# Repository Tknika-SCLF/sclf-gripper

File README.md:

# SCLF Gripper — Firmwarea

[ Euskara ](README.md) | [ English ](README.en.md) | [ Español ](README.es.md)

> Tknikaren SCLF Gripper-erako motor kontrolagailuaren firmwarea.
> STM32G474CEU6 · SimpleFOC · PlatformIO · Antigravity IDE
> Lizentzia: CC BY-SA 4.0

---

> ⚠️ **GARRANTZITSUA:** Proiektu honekin lanean hasi aurretik, mesedez irakurri beti `TASKS.md` fitxategia. Bertan aurkituko duzu proiektuaren uneko egoera zehatza eta garatzaileen arteko hurrengo urratsak zeintzuk diren.

## Hasiera Azkarra

Ingurunea konfiguratuta baduzu dagoeneko:

```bash
# 1. Konpilatu
pio run

# 2. Flasheatu (ST-Link konektatuta)
pio run --target upload

# 3. Serie-monitorea (Gripper-aren USB-C PC-ra)
pio device monitor --baud 115200
```

---

## Ingurunearen Konfigurazioa Hutsetik

### 1. Urratsa — Antigravity Instalatu

Deskargatu eta instalatu Antigravity bere webgune ofizialetik. VSCode/Windsurf-en fork bat da eta modu berean funtzionatzen du.

---

### 2. Urratsa — C/C++ Tools Instalatu

> ⚠️ PlatformIO **ez dago Open VSX-en** (Antigravity-ren marketplace-a). Bi hedapenak eskuz instalatu behar dira `.vsix` fitxategietatik.

**2a.** Joan hona: https://github.com/microsoft/vscode-cpptools/releases/latest

Deskargatu zure sistema eragileari dagokion fitxategia:

| Sistema | Deskargatu beharreko fitxategia |
|---|---|
| Windows (64-bit) | `cpptools-windows-x64.vsix` |
| macOS (Apple Silicon) | `cpptools-macOS-arm64.vsix` |
| macOS (Intel) | `cpptools-macOS-x64.vsix` |
| Linux (64-bit) | `cpptools-linux-x64.vsix` |

**2b.** Antigravity-n: `Hedapenak / Extensions (Ctrl+Shift+X)` → `···` ikonoa (hiru puntu) → **Install from VSIX** → hautatu deskargatutako `.vsix` fitxategia.

---

### 3. Urratsa — PlatformIO Instalatu

**3a.** Joan hona: https://github.com/platformio/platformio-vscode-ide/releases/latest

Ireki azken bertsioaren **"Assets"** atala eta deskargatu fitxategia (adibidez: `platformio-ide-3.3.3.vsix`).

**3b.** Antigravity-n: `Hedapenak / Extensions (Ctrl+Shift+X)` → `···` → **Install from VSIX** → hautatu deskargatutako `.vsix` fitxategia.

**3c.** Berrabiarazi Antigravity. PlatformIOk bere mendekotasunak automatikoki instalatuko ditu lehenengo aldian (2-5 minutu har ditzake).

> ⚠️ **Ohar garrantzitsua:** PlatformIOren instalazioa Antigravity-n ez dago ofizialki onartuta. Konpilazio edo igoera (upload) arazoak badituzu, kontsultatu [Arazoen Konponbidea](#arazoen-konponbidea) atala dokumentu honen amaieran.

---

### 4. Urratsa — cortex-debug Instalatu (ST-Link-ekin debug egiteko)

> 💡 **Zer da Open VSX?** Kode irekiko luzapenen erregistro alternatiboa da (Eclipse Foundation-ek kudeatua). Antigravity-k eta VSCodium-ek ofizialki erabiltzen duten biltegia da, Microsoft-en murrizketak ekiditeko, eta segurua da.

**4a.** Joan hona: https://open-vsx.org/extension/marus25/cortex-debug

Eskuin aldean dagoen **"Version"** goitibeherako menuan, hautatu **"Pre-release"** jartzen EZ duen azken bertsio egonkorra (adibidez: `1.12.1`). Ondoren, sakatu azpian agertzen den **`DOWNLOAD`** botoi morean `.vsix` fitxategia eskuratzeko.

**4b.** Instalatu aurrekoak bezala (Install from VSIX).

**4c.** OpenOCD konfiguratzea:
> 💡 **Albiste ona:** Ez duzu ezer deskargatu edo instalatu behar! PlatformIO-k automatikoki deskargatzen du OpenOCD lehenengo aldiz proiektua konpilatzen edo plakan kargatzen duzunean. Bere kokapena hau izaten da Windows-en:
`C:\Users\ZURE_ERABILTZAILEA\.platformio\packages\tool-openocd\bin\openocd.exe`

*(Cortex-Debug-ek errorea ematen badu OpenOCD ez duela aurkitzen esanez, joan Antigravity-ren ezarpenetara eta ezarri ibilbide hori `cortex-debug.openocdPath` aukeran).*

---

### 5. Urratsa — Git Instalatu

Proiektua klonatzeko Git instalatuta izan behar duzu.

**5a.** Joan hona: https://git-scm.com/downloads

**5b.** Deskargatu eta instalatu zure sistema eragilearen bertsioa (lehenetsitako aukerak mantendu ditzakezu instalazioan).

---

### 6. Urratsa — Proiektua Ireki

```bash
# Klonatu edo kopiatu firmwarearen karpeta
# Ireki Antigravity erro karpetan (platformio.ini dagoen lekuan)
```

Antigravity-n: `File → Open Folder` → hautatu `SCLF_Gripper_firmware/` karpeta.

PlatformIOk automatikoki detektatuko du `platformio.ini` eta honako hauek deskargatuko ditu:
- Platform `ststm32`
- Framework `framework-arduinoststm32`
- Toolchain `toolchain-gccarmnoneeabi`
- `SimpleFOC` liburutegia

---

### 7. Urratsa — Lehenengo Konpilazioa

Antigravity-ren beheko barran, egin klik PlatformIOren ✓ (Build) ikonoan, edo terminaletik:

```bash
pio run
```

**Espero den emaitza:**
```
[SUCCESS] Took X.XX seconds
RAM:   [=         ]  X.X% (used XXXX bytes from 131072 bytes)
Flash: [=         ]  X.X% (used XXXXX bytes from 524288 bytes)
```

Konpilatzen ez badu → ikusi [Arazoen Konponbidea](#arazoen-konponbidea).

---

### 8. Urratsa — ST-Link Konektatu eta Flasheatu

Konektatu ST-Link SCLF Gripper-aren SWD atakara:

| Pin ST-Link | Pad Gripper | Seinalea |
|---|---|---|
| SWDIO | DIO | PA13 |
| SWCLK | CLK | PA14 |
| RST | RST | PG10 |
| GND | GND | — |
| 3.3V | 3V3 | (STM32 soilik elikatzen du, ez encoderra ez driverra) |

> ⚠️ **Elikadura:**
> - ST-Link-aren 3.3V pina **nahikoa da** STM32 flasheatzeko eta encoderra (MT6701) elikatzeko. Bera bakarrik probatu dezakezu 24V konektatu gabe.
> - **BAINA** DRV8316 driverrak eta motorrak **24V kanpokoa** behar dute. Test osoetarako (motorra mugitu), beti konektatu 24V elikadura.

Flasheatu:
```bash
pio run --target upload
```

**Espero den emaitza:** `[SUCCESS]` eta D4 LEDa (PC6) keinuka hasiko da.

#### Aurre-test gomendatua: LED Heartbeat

Test konplexuak egin aurretik, egiaztatu STM32 abiarazten dela:

1. Aldatu `build_src_filter` `platformio.ini`-n:
   ```ini
   build_src_filter = +<../examples/fase0_led_heartbeat>
   ```
2. Flasheatu `pio run --target upload` erabiliz.
3. D4 LEDak 5Hz-ra keinuka egin behar du (200ms). Keinurik ez bada → elikadura edo ST-Link kableatu arazoa.
4. Berreskuratu jatorrizko `build_src_filter` Fase 1.1-era itzuli nahi duzunean.

---

### 9. Urratsa — Encoderra Egiaztatu (Fase 1.1)

> ⚠️ **Baldintzak:** ST-Link-aren 3.3V konektatuta izatea nahikoa da encoderra elikatzeko. Ez da 24V behar fase honetarako.

`fase1_1_mt6701_test`-eko firmware-ak D4 LEDa diagnostiko bisual modura erabiltzen du (Serial gabe):

1. Egiaztatu `build_src_filter` horrela dagoela `platformio.ini`-n:
   ```ini
   build_src_filter = +<../examples/fase1_1_mt6701_test> +<encoder/>
   ```
2. Flasheatu: `pio run --target upload`
3. Begiratu D4 LEDa:

| LED portaera | Esanahia |
|---|---|
| 3 keinu azkar abiaraztean | `setup()` ondo amaituta |
| LED motela (700ms, ~0.7Hz) | Motorra lehen erdibiraketan (0°-180°) |
| LED azkarra (80ms, ~6Hz) | Motorra bigarren erdibiraketan (180°-360°) |
| **Motorra biratzean aldatzen da** ✅ | **MT6701 encoderrak funtzionatzen du!** |
| Beti azkar aldaketarik gabe | SPI-k 0xFFFF bueltatzen du → encoderrak elikadurarik ez |

✅ **LEDak motorra biratzean aldatzen badu, Fase 1.1 gaindituta dago.**

### 9b. Urratsa — Serial Monitor Egiaztatu (USB VCP)

> ✅ **EGOERA:** Ondo funtzionatzen du. Firmwareak `SystemClock_Config` bloke bat dauka `main.cpp`-n STM32G4-ren USB periferikorako behar den HSI48 osziladorea gaitzeko.

1. Konektatu USB-C kable bat Gripperraren eta PCaren artean.
2. Ireki PlatformIOren serie-monitorea (🔌 ikonoa beheko barran) edo sartu:
   ```bash
   pio device monitor --baud 115200
   ```
3. Testaren irteera ikusi beharko zenuke pantailan (Adib. `MT6701 Raw (con o sin 24V): X` edo biratzean aldatzen den balio bat).

---

### 10. Urratsa — Faseen Probak eta Adibideak (`examples/`)

Proiektu honen firmware garapena fase ezberdinetan banatuta dago (ikusi `TASKS.md`). Fase bakoitzean idatzitako kode-probak (test standalone-ak) **`examples/`** karpetaren barruan gordetzen dira.

Hardware berria muntatzen baduzu edo sentsore zehatz bat probatu nahi baduzu:
1. Sartu `examples/` karpetan eta aukeratu fasea (adib. `phase1_1_mt6701_test`, `phase1_2_drv_spi`, `phase1_4_rs485_ping`, `phase3_2_rs485_control` edo `phase3_3_ur_rs485`).
2. **Irakurri karpeta horretan dagoen `README.md` fitxategia** argibide zehatzak ikusteko.
   - **Oharra (Phase 3.3):** RS485 komunikazioa 115200 baud-etan doa UR robot eta URCap/URSim integrazio probarako.
3. Kopiatu bertako `main.cpp` fitxategia eta ordezkatu zure probako `src/main.cpp` fitxategiarekin (edo erabili dagokion ingurunea `platformio.ini`-n). 
4. Konpilatu eta igo (`pio run --target upload`).

---

### 11. Urratsa — IA Agentea Konfiguratu

Antigravity-n barneratuta dagoen IA laguntzailearekin lan egiteko:

1. Ireki agentearen txat-panela (IA ikonoa alboko barran).
2. Saio bakoitzaren hasieran, idatzi:

```
Irakurri testuinguru-fitxategi hauek lagundu aurretik:
- AGENT.md   (hardwarea, pinak, arkitektura)
- MEMORY.md  (uneko egoera, kalibratutako parametroak)
- TASKS.md   (orain lantzen ari naizen zeregina)
- RULES.md   (sortutako kodeak errespetatu behar dituen arauak)
```

3. Gero, deskribatu zein zeregin landu nahi duzun `TASKS.md`-tik.

---

## Proiektuaren Egitura

```
SCLF_Gripper_firmware/
│
├── src/
│   ├── main.cpp                    ← Sarrera puntua. 0 FASEA: smoke test
│   ├── config/
│   │   └── pins.h                  ← Pin GUZTIAK. Eskematikoarekin egiaztatuta.
│   ├── encoder/
│   │   ├── MT6701.h                ← Encoder-aren APIa (eskeletoa prest)
│   │   └── MT6701.cpp              ← 1.1 FASEAN inplementatu
│   ├── motor/
│   │   ├── DRV8316.h               ← Gate driver-aren APIa (eskeletoa prest)
│   │   └── DRV8316.cpp             ← 1.2 FASEAN inplementatu
│   ├── comms/
│   │   ├── RS485.h                 ← RS-485 APIa
│   │   └── RS485.cpp               ← RS-485 inplementazioa
│   └── faults/
│       ├── FaultManager.h          ← Akats kudeatzailearen APIa (eskeletoa prest)
│       └── FaultManager.cpp        ← 6 FASEAN inplementatu
│
├── lib/                            ← Bertako liburutegiak
├── test/                           ← PlatformIO Unity testak (8 FASEA)
│
├── examples/
│   ├── phase0_led_heartbeat/        ← 0 Fasea: LED keinua menpekotasunik gabe
│   ├── phase1_1_mt6701_test/        ← 1.1 Fasea: MT6701 encoder proba SPI bidez
│   ├── phase1_2_drv_spi/            ← 1.2 Fasea: DRV8316 SPI komunikazio proba
│   ├── phase1_3_open_loop_v_control/← 1.3 Fasea: Begizta irekiko tentsio kontrola
│   ├── phase1_4_rs485_ping/         ← 1.4 Fasea: RS-485 PING/PONG oinarrizkoa
│   ├── phase2_1_foc_open_loop/      ← 2.1 Fasea: FOC begizta irekiko kontrola
│   ├── phase2_2_foc_closed_loop/    ← 2.2 Fasea: FOC begizta itxia
│   ├── phase3_1_rs485_basic/        ← 3.1 Fasea: RS-485 oinarrizko protokoloa
│   ├── phase3_2_rs485_control/      ← 3.2 Fasea: RS-485 kontrol komando osoak
│   └── phase3_3_ur_rs485/           ← 3.3 Fasea: UR Robot / URCap RS-485 integrazioa
│
├── .vscode/
│   ├── settings.json               ← IDE konfigurazioa (IntelliSense, formatua)
│   ├── extensions.json             ← Gomendatutako hedapenak
│   └── launch.json                 ← Debug ST-Link cortex-debug-ekin
│
├── platformio.ini                  ← Build eta upload konfigurazioa
├── .clang-format                   ← Kode estiloa (gordetzean aplikatzen da)
├── .gitignore
│
├── AGENT.md    ← 📋 IA agentearentzako testuingurua
├── MEMORY.md   ← 🧠 Proiektuaren egoera iraunkorra
├── TASKS.md    ← ✅ Backlog osoa faseka
├── RULES.md    ← 📏 Proiektuaren arauak
└── SRS.md      ← 📄 Eskakizunen zehaztapena
```

### Arkitektura Modularraren Azalpena

Proiektu hau berezibila eta antolatua izateko garatu da:
* **`main.cpp` ("Zuzendaria"):** FOC kontrol-begizta eta hasierako konfigurazioa soilik ditu. Ez da kode nahaspilatuz betetzen.
* **`.cpp` espezifikoak ("Musikariak"):** Txip bakoitzak bere artxibo dedikatua dauka bere funtzio jakingarriagoetarako (adibidez `MT6701.cpp` posizioa zuzenean irakurtzeko erroreak kontrolatuz, edo `DRV8316.cpp` tenperatura edo zirkuitulabur kasuez informatzeko).
* **Modu honetan:** `main.cpp`-ak oinarrizko aginduak ematen ditu, eta modulu bakoitzak badaki bere tresna zehazki nola erabili, etorkizuneko hardware aldaketak izugarri erraztuz.

### Hardware Segurtasuna eta Garapena (⚠️ OSO GARRANTZITSUA)

Antigravity barruan proiektu hau garatzean, [Arau Zorrotzak (RULES.md)](RULES.md) ezarrita daude:
1. **Debekatuta dago Blokeatzea:** Inoiz ez erabili `delay()`, `HAL_Delay` edo `while()` begizta infiniturik FOC exekuzioan. SimpleFOC-ek mikroren %100 erabiltzea eskatzen du korrontea denbora errealean kalkulatzeko. Mikroa "lotaratzeak" motorra edo driverra segundo batean erretzea ekar dezake.
2. **`foc-hardware-setup` Tresna (Skill):** Kodea garatzen hasi aurretik, gure IA laguntzaileak badu tresna espezifiko bat KiCad-eko eskema elektrikoak zuzenean irakurtzeko (`.kicad_sch`) eta `pins.h` fitxategi ezin hobea sortzeko, inolako giza-akatsik gabe. Zure laguna da, erabili proiektuaren azken pinen zehaztapenak egiaztatzeko!
3. **Cortex-Debug Magia:** ST-Link v2 klonarekin edo jatorrizkoarekin, Plaka zuzenean kontrolatu eta pausatu daiteke. Programan aldagairen batek zergatik hartzen duen balio jakin bat deskubritu nahi bada, jarri Breakpoint (eten-puntu) bat Antigravity-n, eta kodea zuzen-zuzenean pausatuko da STM32-an!

---

## PlatformIO Komando Erabilienak

```bash
pio run                          # Konpilatu
pio run --target upload          # Konpilatu eta flasheatu (ST-Link)
pio run --target upload_dfu      # USB DFU bidez flasheatu (BOOT + RST)
pio device monitor               # Serie-monitorea (USB VCP, 115200 baud)
pio test                         # Test unitarioak exekutatu
pio run --target clean           # Konpilazio-artefaktuak garbitu
pio lib install "Simple FOC"     # Eskuz instalatu liburutegia
pio pkg update                   # Plataforma eta liburutegiak eguneratu
```

---

## DFU Bootloader (Flasheatu ST-Link gabe)

ST-Link erabilgarririk ez baduzu, USB DFU bidez flashea dezakezu:

1. Mantendu sakatuta **BOOT** (PB8) botoia.
2. Sakatu eta askatu **RESET** (PG10) botoia.
3. Askatu **BOOT**.
4. Gripperra DFU gailu gisa agertuko da PCan.
5. Aldatu `upload_protocol = dfu` fitxategian `platformio.ini`.
6. Exekutatu `pio run --target upload`.

> 💡 **Oharra ST-Link gabe DFU erabiltzearen inguruan (PA9 pina):**
> Ohiko STM32etan (F1/F4), USB kablea konektatuta dagoela nabaritzeko (VBUS sensing) `PA9` pina erabiltzen da. Gure diseinuan, ordea, `PA9` pina motorraren B fasera (DRV8316) konektatuta dago (`PIN_BH`). Baina ez larritu! **STM32G4 familiak VBUS sentsorea hardware bidez desgaituta dauka** bere Bootloader nagusian (AN2606). Hori dela eta, DFU moduak primeran funtzionatuko du soilik `PA11` eta `PA12` datu-pinak erabiliz, hardware aldaketen beharrik gabe.
> 
> **⚠️ KONTUZ Arazketa (Debugging) egiteko orduan:**
> Kontuan izan USB DFU metodoa "itsu-itsuan pentsatua" dela: kodearen irudia (`.bin`) mikroaren memorian kargatzeko **soilik** balio du. Garapen-fasean zaudenean eta SimpleFOC motorraren ezusteko portaera bat ikertu behar duzunean, **ezinbestekoa da ST-Link (edo SWD) bat erabiltzea**. ST-Link batek zuzenean ARM Cortex muinera konektatzen zaitu `PA13/PA14` bidez, eta aukera ematen dizu kodea pausatzeko (Breakpoints), aldagaien balioak denbora errealean irakurtzeko eta exekuzioa lerroz lerro aztertzeko VS Code-n. USB-ak ezin du horrelakorik egin.

---

## Arazoen Konponbidea

### PlatformIOk ez du konpilatzen / toolchain errorea
```bash
# STM32 plataforma berrinstalatu
pio platform install ststm32

# Garbitu eta berriro konpilatu
pio run --target clean && pio run
```

### ST-Link-ek ez du plaka detektatzen
- Egiaztatu ST-Link-eko GNDa gripperreko GND-ra konektatuta dagoela.
- Egiaztatu plakak elikadura duela (PWR LEDa piztuta).
- Probatu `openocd -f interface/stlink.cfg -f target/stm32g4x.cfg` terminalean.
- OpenOCD-k huts egiten badu: eguneratu ST-Link firmwarea STM32CubeProgrammer-etik.

### USB VCP ez da agertzen PCan
- Instalatu STM32 VCP kontrolatzailea (driverra): https://www.st.com/en/development-tools/stsw-stm32102.html (Windows soilik)
- Linux/macOS sistemetan ez dago kontrolatzailerik behar. Egiaztatu `ls /dev/ttyACM*` erabiliz.

### LEDak ez du keinurik egiten flasheatu ondoren
- **Ziurtatu erlojuaren konfigurazioa duzula:** STM32duino framework-ak `-DUSBCON` flag-ekin (berez aktibatuta proiektu honetan) USB CDC possesses `setup()` baino **lehenago** hasieratzen du. `main.cpp`-ren amaieran HSI48 aktibatzen duen `SystemClock_Config(void)` funtzioa falta bada, firmwarea blokeatu egiten da.
- Probatu `examples/fase0_led_heartbeat` (LED soilik, menpekotasunik gabe). Horrek ere funtzionatzen ez badu → elikadura edo kableatu arazoa.

### Serial Monitoreak ez du daturik erakusten (pantaila hutsik)
- Ziurtatu COM ataka zuzenean konektatzen zarela. ST-Link-ek COM bereizi bat sortzen du: COM hori beti isilik egongo da. Bilatu "STM32 Virtual COM Port" Gailu Kudeatzailean.
- Flasheatu berri baduzu, Windows-ek segundo bat behar izan dezake USB berria ezagutzeko. PlatformIO-k ataka zaharrean monitorea ireki badu, "zintzilik" geratuko da. Kantzelatu terminalean `Ctrl+C` erabiliz eta exekutatu `pio device monitor` berriro.

### IntelliSense-k ez du `Arduino.h` edo STM32 header-ak aurkitzen
- Itxaron PlatformIOk lehenengo konpilazioa amaitu arte (includes indizea sortzen du).
- Arazoak jarraitzen badu: `Ctrl+Shift+P` → "C/C++: Reset IntelliSense Database".

### Antigravity / PlatformIO ez da plakarekin komunikatzen
- Hau komunitatean dokumentatuta dagoen arazo ezaguna da. PlatformIO Antigravity-n
  ez dago ofizialki onartuta. Konpilazioak funtzionatzen badu baina igotzeak (upload) huts egiten badu,
  saiatu `pio run --target upload` exekutatzen **barne terminaletik**, PlatformIOko
  UI botoiaren ordez.

### PlatformIOk "ms-vscode.cpptools" eskatzen du etengabe (Menpekotasunen Kirurgia)
PlatformIOk batzuetan Microsoft-en hedapena instalatzea exijitzen du, nahiz eta eskuz instalatuta izan. Arazoa konpontzeko:
1. Itxi Antigravity erabat.
2. Ireki fitxategi-esploratzailea eta joan hona: `%USERPROFILE%\.antigravity\extensions\` (Windows) edo `~/.antigravity/extensions/` (Linux/macOS).
3. Sartu `platformio.platformio-ide-...` izeneko karpetan.
4. Ireki `package.json` fitxategia testu-editore batekin.
5. Bilatu `"extensionDependencies": ["ms-vscode.cpptools"]` lerroa.
6. Utzi hutsik horrela: `"extensionDependencies": []`
7. Gorde fitxategia eta berrabiarazi Antigravity.

---

## Erreferentziazko Hardwarea

| Osagaia | Zatia | Datasheet-a |
|---|---|---|
| MCU | STM32G474CEU6 | [ST.com](https://www.st.com/resource/en/reference_manual/rm0440-stm32g4-series-advanced-armbased-32bit-mcus-stmicroelectronics.pdf) |
| Gate Driver | DRV8316CRRGFR | [TI.com](https://www.ti.com/lit/ds/symlink/drv8316.pdf) |
| Encoder | MT6701QT | [Magntek](https://www.magntek.com.cn/upload/MT6701_Rev.1.8.pdf) |
| RS-485 | MAX3485 | [Analog](https://www.analog.com/media/en/technical-documentation/data-sheets/MAX3483-MAX3491.pdf) |
| SimpleFOC | v2.x | [docs.simplefoc.com](https://docs.simplefoc.com) |

---

*Tknikak diseinatua — Licensed under CC BY-SA 4.0*

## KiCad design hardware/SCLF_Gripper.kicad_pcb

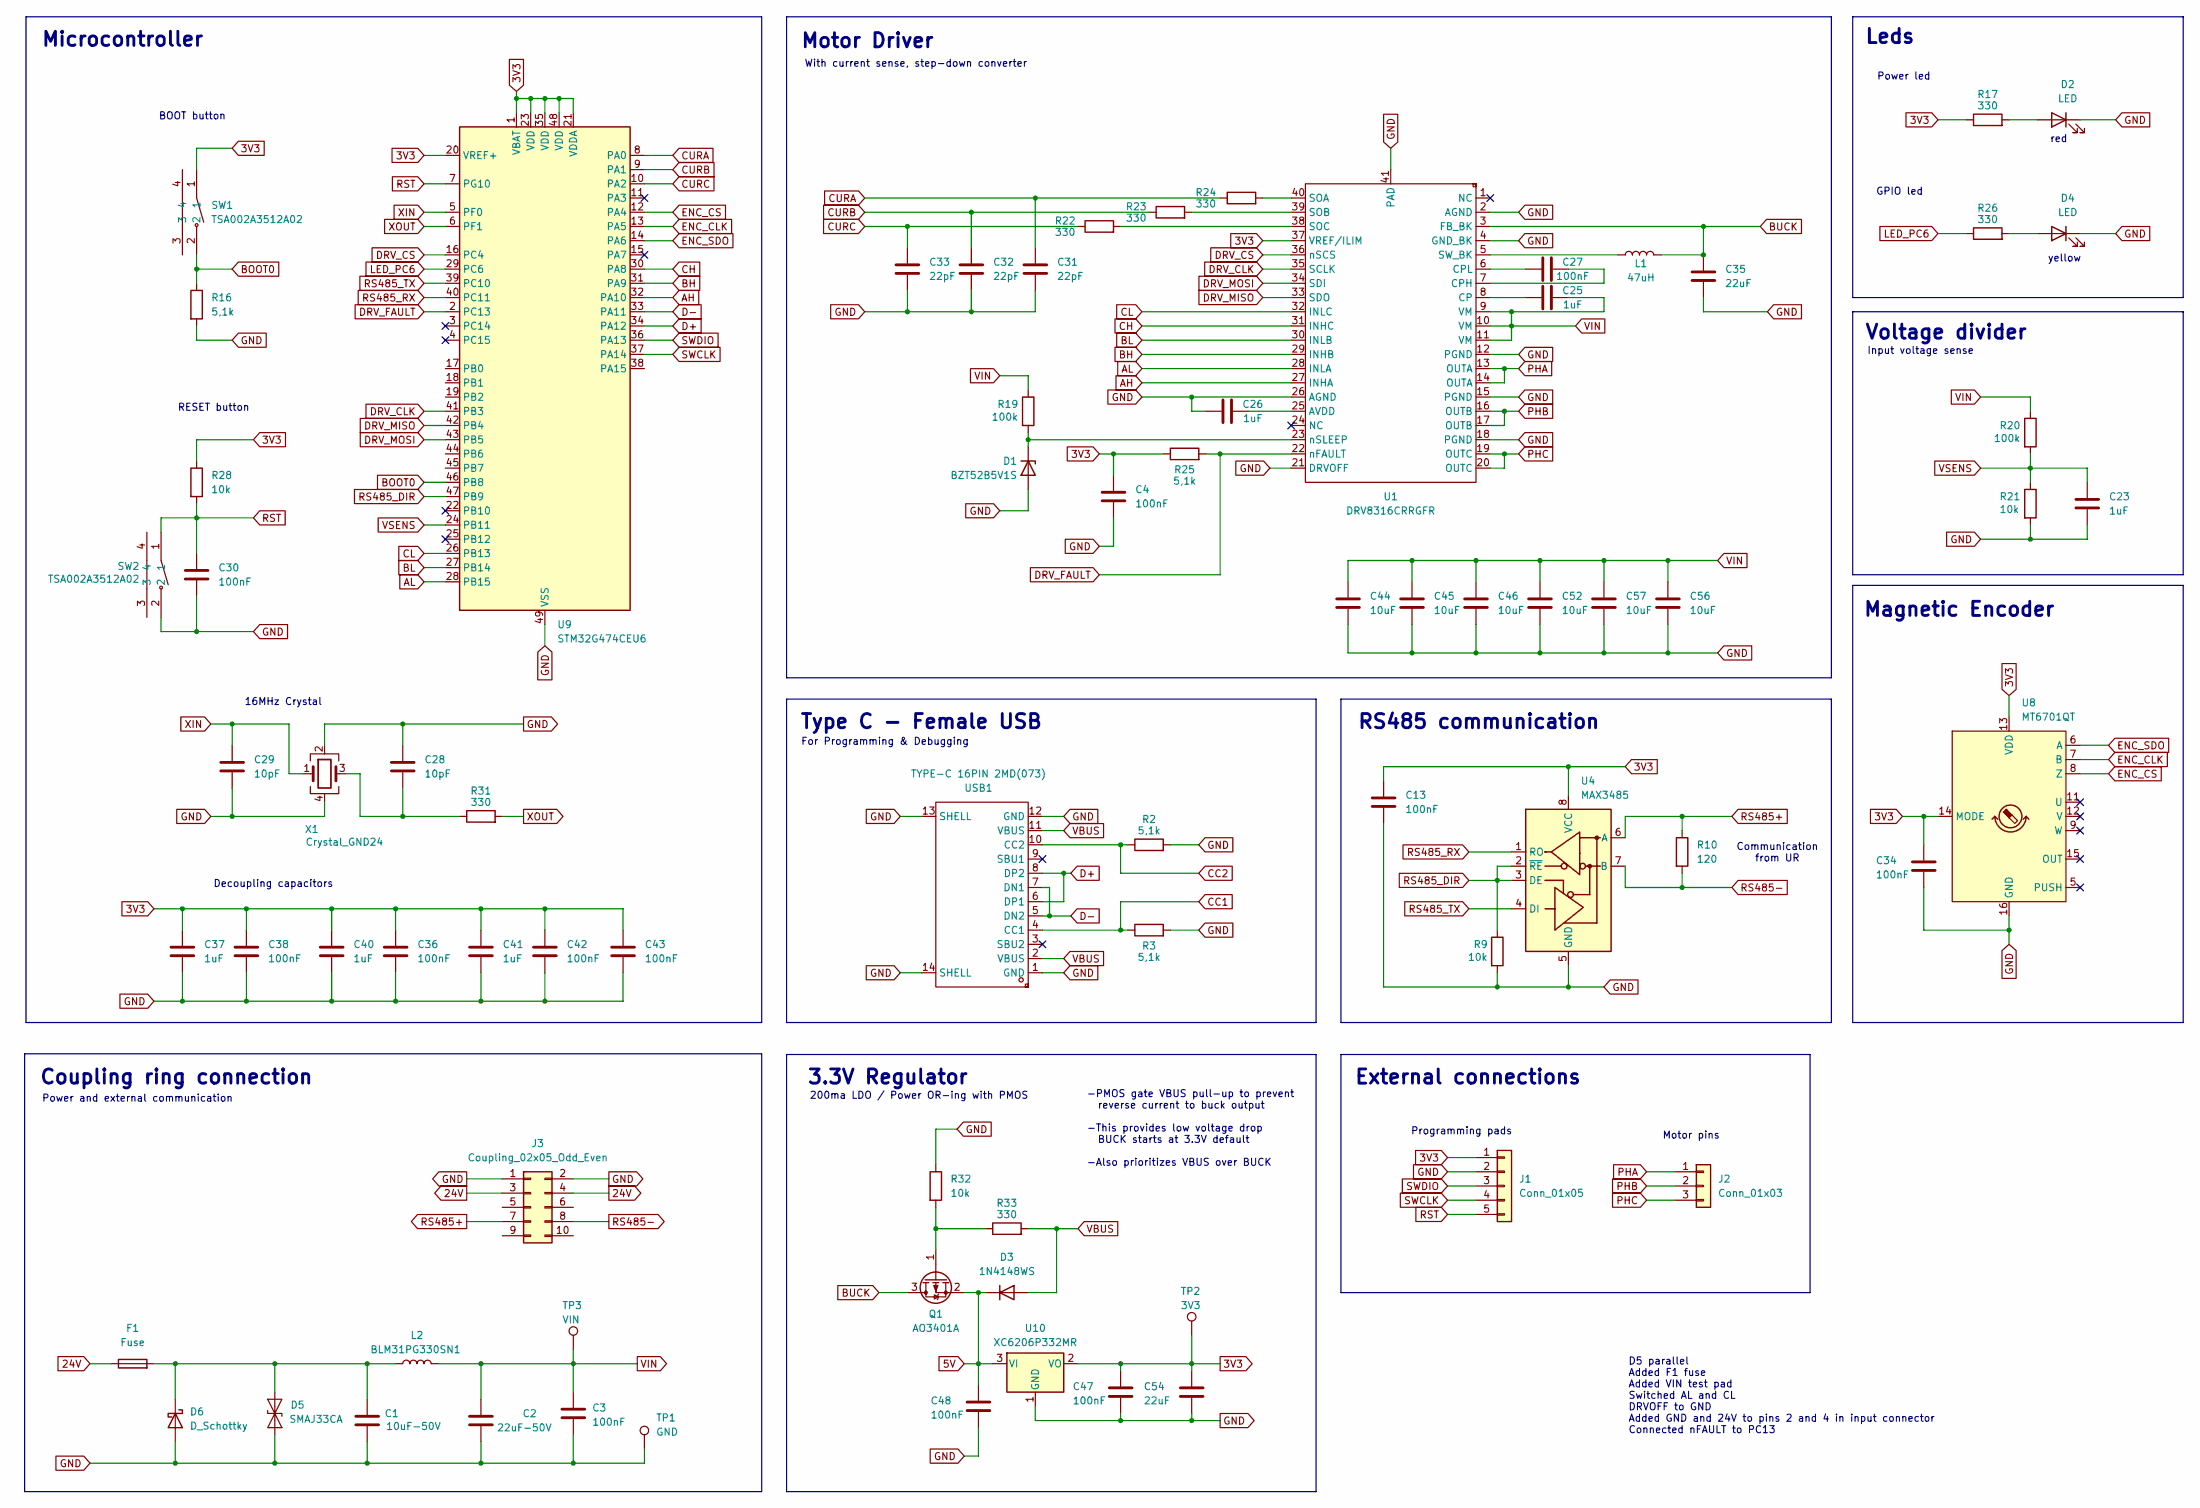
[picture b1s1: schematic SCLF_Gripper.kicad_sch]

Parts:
C1: 10uF-50V; C_1210_3225Metric; LCSC Part C53084458
C2: 22uF-50V; C_2220_5750Metric; LCSC Part C784103
C3, C13: 100nF; C_0603_1608Metric; LCSC Part C14663
C4, C27, C30, C34, C36, C38, C42, C43, C47, C48: 100nF; C_0402_1005Metric; LCSC Part C307331
C23, C25, C26, C37, C40, C41: 1uF; C_0402_1005Metric; LCSC Part C52923
C28, C29: 10pF; C_0402_1005Metric; LCSC Part C32949
C31, C32, C33: 22pF; C_0402_1005Metric; LCSC Part C1555
C35, C54: 22uF; C_0603_1608Metric; LCSC Part C59461
C44, C45, C46, C52, C56, C57: 10uF; C_0805_2012Metric; LCSC Part C440198
D1: BZT52B5V1S; D_SOD-323; LCSC Part C19077434
D2: LED; LED_0603_1608Metric; LCSC Part C2286
D3: 1N4148WS; D_SOD-323_HandSoldering; LCSC Part C2128
D4: LED; LED_0603_1608Metric; LCSC Part C72038
D5: SMAJ33CA; D_SMA; LCSC Part C19077549
D6: D_Schottky; D_SMC; LCSC Part C908690
F1: Fuse; Fuse_1206_3216Metric_Pad1.42x1.75mm_HandSolder; LCSC Part C41342
J1: Conn_01x05; PogoPinPads_1x05_P2.54mm
J2: Conn_01x03; PinHeader_1x03_P2.54mm_Vertical_Center
J3: Coupling_02x05_Odd_Even; Coupling_Conn_2x05_P2.54mm
L1: 47uH; L_Changjiang_FTC303015D; LCSC Part C96151
L2: BLM31PG330SN1; L_1206_3216Metric; LCSC Part C74090
Q1: AO3401A; SOT-23; LCSC Part C15127
R2, R3, R16, R25: 5,1k; R_0402_1005Metric; LCSC Part C25905
R9, R21, R28, R32: 10k; R_0402_1005Metric; LCSC Part C25744
R10: 120; R_0402_1005Metric; LCSC Part C25079
R17, R22, R23, R24, R26, R31, R33: 330; R_0402_1005Metric; LCSC Part C25104
R19, R20: 100k; R_0402_1005Metric; LCSC Part C25741
SW1, SW2: TSA002A3512A02; SW-SMD_BZCN_TSA002A35XXX; LCSC Part C2888932
TP1: GND; TestPoint_Pad_D1.0mm
TP2: 3V3; TestPoint_Pad_D1.0mm
TP3: VIN; TestPoint_Pad_D1.0mm
U1: DRV8316CRRGFR; VQFN-40_L7.0-W5.0-P0.50-BL-EP5.7; LCSC Part C5447274
U4: MAX3485; SOIC-8_3.9x4.9mm_P1.27mm; LCSC Part C8963
U8: MT6701QT; QFN-16-1EP_3x3mm_P0.5mm_EP1.7x1.7mm; LCSC Part C2913974
U9: STM32G474CEU6; QFN-48-1EP_7x7mm_P0.5mm_EP5.6x5.6mm; LCSC Part C1235412
U10: XC6206P332MR; SOT-23-3; LCSC Part C5446
USB1: TYPE-C 16PIN 2MD(073); USB-C-SMD_TYPE-C-6PIN-2MD-073; LCSC Part C2765186
X1: Crystal_GND24; Crystal_SMD_Abracon_ABM8AIG-4Pin_3.2x2.5mm; LCSC Part C1669787

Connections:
3V3: C4.1, C13.1, C34.1, C36.1, C37.1, C38.1, C40.1, C41.1, C42.1, C43.1, C47.1, C54.1, J1.1, R17.1, R25.1, R28.1, SW1.1, TP2.1, U1.37 (VREF/ILIM), U4.8 (VCC), U8.13 (VDD), U8.14 (MODE), U9.1 (VBAT), U9.20 (VREF+), U9.21 (VDDA), U9.23 (VDD), U9.35 (VDD), U9.48 (VDD), U10.2 (VO)
5V: C48.1, D3.1 (K), Q1.2 (S), U10.3 (VI)
24V: F1.1, J3.3, J3.4
AH: U1.27 (INHA), U9.32 (PA10)
AL: U1.28 (INLA), U9.28 (PB15)
BH: U1.29 (INHB), U9.31 (PA9)
BL: U1.30 (INLB), U9.27 (PB14)
BOOT0: R16.1, SW1.2, U9.46 (PB8)
BUCK: C35.1, L1.2, Q1.3 (D), U1.3 (FB_BK)
CC1: R3.1, USB1.4 (CC1)
CC2: R2.1, USB1.10 (CC2)
CH: U1.31 (INHC), U9.30 (PA8)
CL: U1.32 (INLC), U9.26 (PB13)
CURA: C31.1, R24.1, U9.8 (PA0)
CURB: C32.1, R23.1, U9.9 (PA1)
CURC: C33.1, R22.1, U9.10 (PA2)
D+: U9.34 (PA12), USB1.6 (DP1), USB1.8 (DP2)
D-: U9.33 (PA11), USB1.5 (DN2), USB1.7 (DN1)
DRV_CLK: U1.35 (SCLK), U9.41 (PB3)
DRV_CS: U1.36 (nSCS), U9.16 (PC4)
DRV_FAULT: R25.2, U1.22 (nFAULT), U9.2 (PC13)
DRV_MISO: U1.33 (SDO), U9.42 (PB4)
DRV_MOSI: U1.34 (SDI), U9.43 (PB5)
ENC_CLK: U8.7 (B), U9.13 (PA5)
ENC_CS: U8.8 (Z), U9.12 (PA4)
ENC_SDO: U8.6 (A), U9.14 (PA6)
GND: C1.2, C2.2, C3.2, C4.2, C13.2, C23.2, C26.1, C28.1, C29.2, C30.2, C31.2, C32.2, C33.2, C34.2, C35.2, C36.2, C37.2, C38.2, C40.2, C41.2, C42.2, C43.2, C44.2, C45.2, C46.2, C47.2, C48.2, C52.2, C54.2, C56.2, C57.2, D1.2 (A), D2.1 (K), D4.1 (K), D5.2 (A2), D6.2 (A), J1.2, J3.1, J3.2, R2.2, R3.2, R9.2, R16.2, R21.2, R32.1, SW2.2, TP1.1, U1.2 (AGND), U1.4 (GND_BK), U1.12 (PGND), U1.15 (PGND), U1.18 (PGND), U1.21 (DRVOFF), U1.26 (AGND), U1.41 (PAD), U4.5 (GND), U8.16 (GND), U8.17 (GND), U9.49 (VSS), U10.1 (GND), USB1.1 (GND), USB1.12 (GND), USB1.13 (SHELL), USB1.14 (SHELL), X1.2, X1.4
LED_PC6: R26.1, U9.29 (PC6)
unnamed: C28.2, R31.1, X1.3
unnamed: D1.1 (K), R19.2, U1.23 (nSLEEP)
unnamed: D2.2 (A), R17.2
unnamed: D4.2 (A), R26.2
unnamed: C1.1, D5.1 (A1), D6.1 (K), F1.2, L2.1
unnamed: Q1.1 (G), R32.2, R33.1
unnamed: C26.2, U1.25 (AVDD)
unnamed: C25.1, U1.8 (CP)
unnamed: C27.2, U1.7 (CPH)
unnamed: C27.1, U1.6 (CPL)
unnamed: R24.2, U1.40 (SOA)
unnamed: R23.2, U1.39 (SOB)
unnamed: R22.2, U1.38 (SOC)
unnamed: L1.1, U1.5 (SW_BK)
PHA: J2.1, U1.13 (OUTA), U1.14 (OUTA)
PHB: J2.2, U1.16 (OUTB), U1.17 (OUTB)
PHC: J2.3, U1.19 (OUTC), U1.20 (OUTC)
RS485+: J3.7, R10.1, U4.6 (A)
RS485-: J3.8, R10.2, U4.7 (B)
RS485_DIR: R9.1, U4.2 (~RE), U4.3 (DE), U9.47 (PB9)
RS485_RX: U4.1 (RO), U9.40 (PC11)
RS485_TX: U4.4 (DI), U9.39 (PC10)
RST: C30.1, J1.5, R28.2, SW2.1, U9.7 (PG10)
SWCLK: J1.4, U9.37 (PA14)
SWDIO: J1.3, U9.36 (PA13)
VBUS: D3.2 (A), R33.2, USB1.2 (VBUS), USB1.11 (VBUS)
VIN: C2.1, C3.1, C25.2, C44.1, C45.1, C46.1, C52.1, C56.1, C57.1, L2.2, R19.1, R20.1, TP3.1, U1.9 (VM), U1.10 (VM), U1.11 (VM)
VSENS: C23.1, R20.2, R21.1, U9.24 (PB11)
XIN: C29.1, U9.5 (PF0), X1.1
XOUT: R31.2, U9.6 (PF1)

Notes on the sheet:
Communication from UR
Leds
red
For Programming & Debugging
16MHz Crystal
Motor pins
200ma LDO / Power OR-ing with PMOS
BOOT button
yellow
Decoupling capacitors
-PMOS gate VBUS pull-up to prevent reverse current to buck output -This provides low voltage drop BUCK starts at 3.3V default -Also prioritizes VBUS over BUCK
With current sense, step-down converter
Motor Driver
External connections
3.3V Regulator
Magnetic Encoder
Microcontroller
Power led
RS485 communication
RESET button
Coupling ring connection
Input voltage sense
D5 parallel Added F1 fuse Added VIN test pad Switched AL and CL DRVOFF to GND Added GND and 24V to pins 2 and 4 in input connector Connected nFAULT to PC13
Power and external communication
GPIO led
Voltage divider
Programming pads
Type C - Female USB

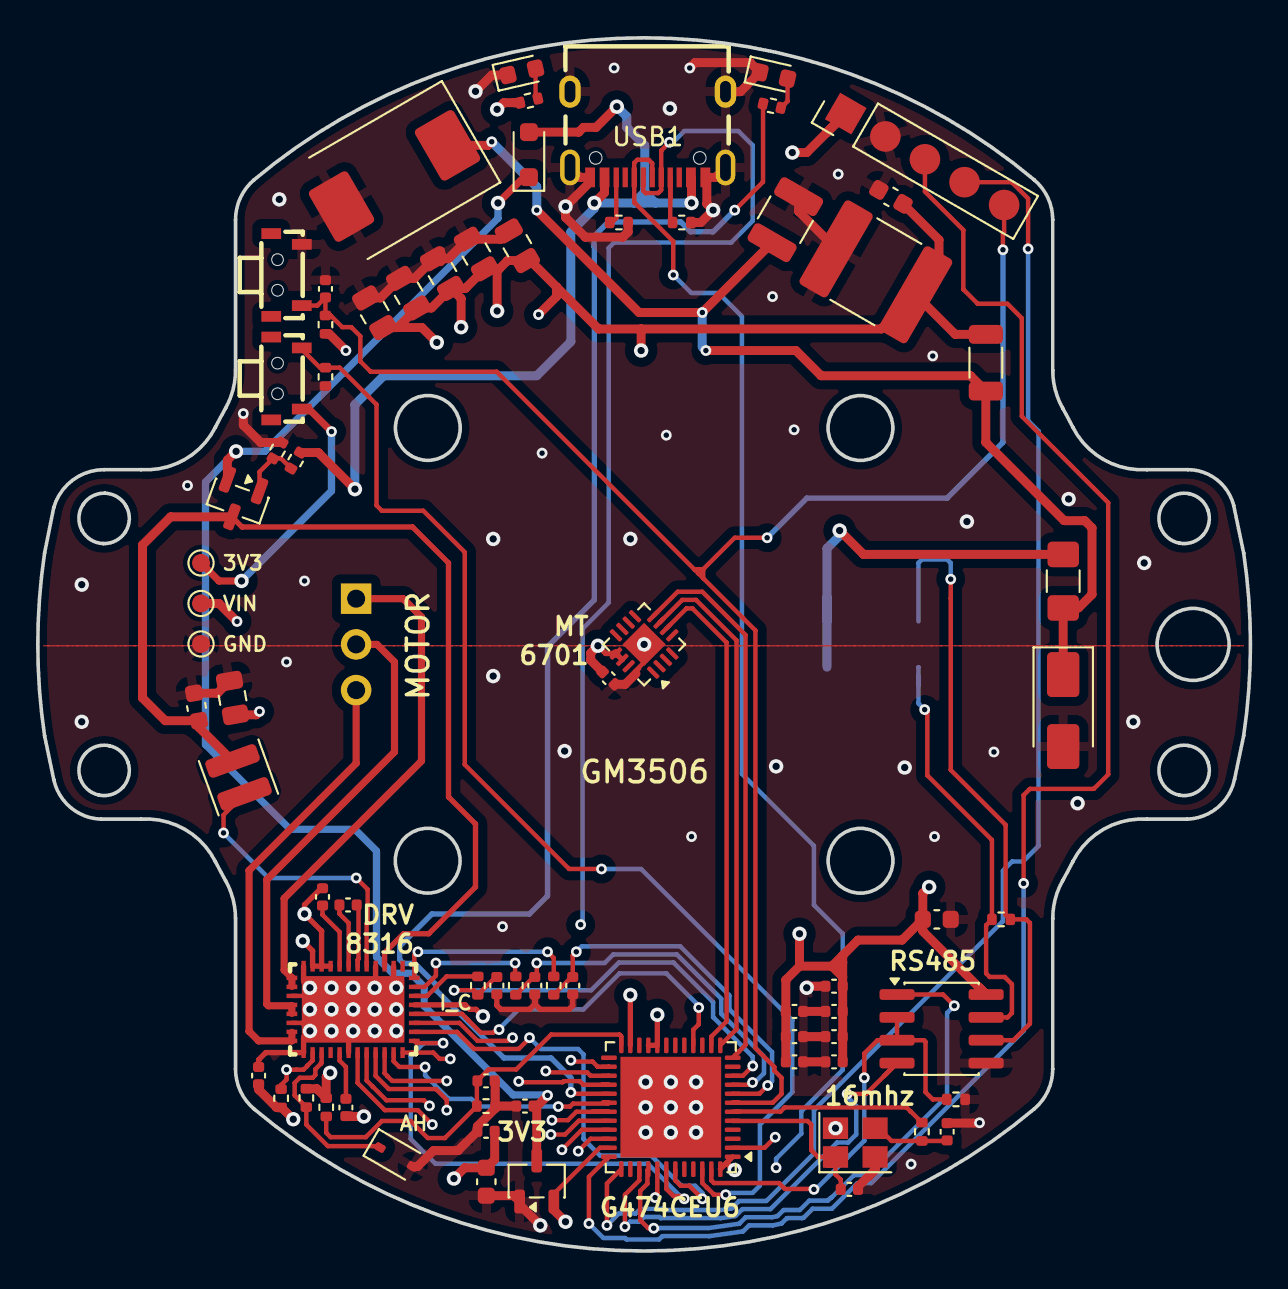
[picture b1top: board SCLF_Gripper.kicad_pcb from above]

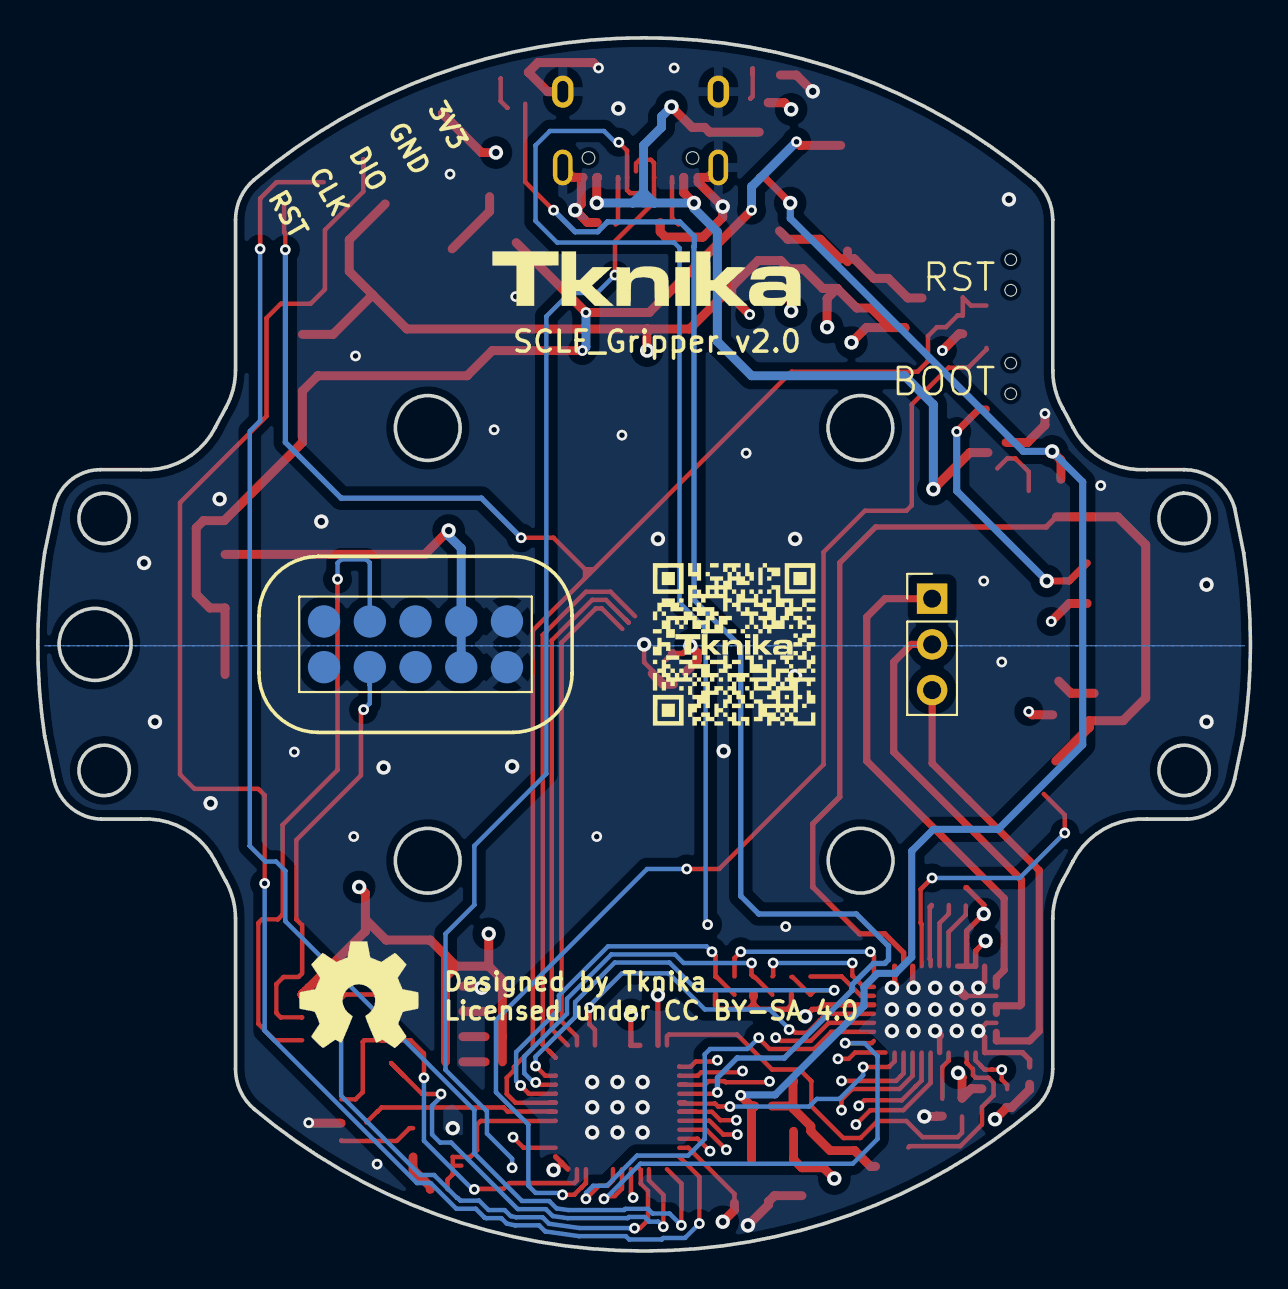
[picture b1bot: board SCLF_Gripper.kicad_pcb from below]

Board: 4 copper layers, 67.4 x 67.4 mm, 77 parts (3 on the bottom side), 58 nets.

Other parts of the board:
G: LOGO; QR

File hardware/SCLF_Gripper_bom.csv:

"Reference";"Qty";"Value";"DNP";"Exclude from BOM";"Exclude from Board";"Footprint";"Datasheet"
"C1";"1";"10uF-50V";"";"";"";"Capacitor_SMD:C_1210_3225Metric";"https://www.lcsc.com/datasheet/C53084458.pdf"
"C2";"1";"22uF-50V";"";"";"";"Capacitor_SMD:C_2220_5750Metric";"https://www.lcsc.com/datasheet/C784103.pdf"
"C3,C13";"2";"100nF";"";"";"";"Capacitor_SMD:C_0603_1608Metric";"https://www.lcsc.com/datasheet/C14663.pdf,~"
"C23,C25,C26,C37,C40,C41";"6";"1uF";"";"";"";"Capacitor_SMD:C_0402_1005Metric";"https://www.lcsc.com/datasheet/C52923.pdf,~"
"C27,C30,C34,C36,C38,C42,C43,C47,C48";"9";"100nF";"";"";"";"Capacitor_SMD:C_0402_1005Metric";"https://www.lcsc.com/datasheet/C307331.pdf,~"
"C28,C29";"2";"10pF";"";"";"";"Capacitor_SMD:C_0402_1005Metric";"https://www.lcsc.com/datasheet/C32949.pdf,~"
"C31,C32,C33";"3";"22pF";"";"";"";"Capacitor_SMD:C_0402_1005Metric";"https://www.lcsc.com/datasheet/C1555.pdf,~"
"C35,C54";"2";"22uF";"";"";"";"Capacitor_SMD:C_0603_1608Metric";"https://www.lcsc.com/datasheet/C59461.pdf,~"
"C44,C45,C46,C52,C56,C57";"6";"10uF";"";"";"";"Capacitor_SMD:C_0805_2012Metric";"https://www.lcsc.com/datasheet/C440198.pdf,~"
"D1";"1";"BZT52B5V1S";"";"";"";"Diode_SMD:D_SOD-323";"https://www.lcsc.com/datasheet/C19077434.pdf"
"D2,D4";"2";"LED";"";"";"";"LED_SMD:LED_0603_1608Metric";"https://www.lcsc.com/datasheet/C2286.pdf,~"
"D3";"1";"1N4148WS";"";"";"";"Diode_SMD:D_SOD-323_HandSoldering";"https://www.lcsc.com/datasheet/C2128.pdf"
"D5";"1";"SMAJ33CA";"";"";"";"Diode_SMD:D_SMA";"https://www.lcsc.com/datasheet/C19077549.pdf"
"D6";"1";"D_Schottky";"";"";"";"Diode_SMD:D_SMC";"https://www.lcsc.com/datasheet/C908690.pdf"
"J1";"1";"Conn_01x05";"";"Excluido del BOM";"";"Aimar:PogoPinPads_1x05_P2.54mm";"~"
"J2";"1";"Conn_01x03";"";"Excluido del BOM";"";"Connector_PinHeader_2.54mm:PinHeader_1x03_P2.54mm_Vertical";"~"
"J3";"1";"Coupling_02x05_Odd_Even";"";"Excluido del BOM";"";"Aimar:Coupling_Conn_2x05_P2.54mm";"~"
"L1";"1";"47uH";"";"";"";"Inductor_SMD:L_Changjiang_FTC303015D";"https://www.lcsc.com/datasheet/C96151.pdf"
"L2";"1";"BLM31PG330SN1";"";"";"";"Inductor_SMD:L_1206_3216Metric";"https://www.lcsc.com/datasheet/C74090.pdf"
"Q1";"1";"AO3401A";"";"";"";"Package_TO_SOT_SMD:SOT-23";"https://www.lcsc.com/datasheet/C15127.pdf"
"R2,R3,R16,R25";"4";"5,1k";"";"";"";"Resistor_SMD:R_0402_1005Metric";"https://www.lcsc.com/datasheet/C25905.pdf,~"
"R9,R21,R28,R32";"4";"10k";"";"";"";"Resistor_SMD:R_0402_1005Metric";"https://www.lcsc.com/datasheet/C25744.pdf,~"
"R10";"1";"120";"";"";"";"Resistor_SMD:R_0402_1005Metric";"https://www.lcsc.com/datasheet/C25079.pdf"
"R17,R22,R23,R24,R26,R31,R33";"7";"330";"";"";"";"Resistor_SMD:R_0402_1005Metric";"https://www.lcsc.com/datasheet/C25104.pdf,~"
"R19,R20";"2";"100k";"";"";"";"Resistor_SMD:R_0402_1005Metric";"https://www.lcsc.com/datasheet/C25741.pdf,~"
"SW1,SW2";"2";"TSA002A3512A02";"";"";"";"USB:SW-SMD_BZCN_TSA002A35XXX";"https://www.lcsc.com/datasheet/C2888932.pdf"
"U1";"1";"DRV8316CRRGFR";"";"";"";"USB:VQFN-40_L7.0-W5.0-P0.50-BL-EP5.7";"https://www.lcsc.com/datasheet/C5447274.pdf"
"U4";"1";"MAX3485";"";"";"";"Package_SO:SOIC-8_3.9x4.9mm_P1.27mm";"https://www.lcsc.com/datasheet/C8963.pdf"
"U8";"1";"MT6701QT";"";"";"";"Package_DFN_QFN:QFN-16-1EP_3x3mm_P0.5mm_EP1.7x1.7mm";"https://www.lcsc.com/datasheet/C2913974.pdf"
"U9";"1";"STM32G474CEU6";"";"";"";"Package_DFN_QFN:QFN-48-1EP_7x7mm_P0.5mm_EP5.6x5.6mm";"https://www.lcsc.com/datasheet/C1235412.pdf"
"U10";"1";"XC6206P332MR";"";"";"";"Package_TO_SOT_SMD:SOT-23-3";"https://www.lcsc.com/datasheet/C5446.pdf"
"USB1";"1";"TYPE-C 16PIN 2MD(073)";"";"";"";"USB:USB-C-SMD_TYPE-C-6PIN-2MD-073";"https://www.lcsc.com/datasheet/C2765186.pdf"
"X1";"1";"Crystal_GND24";"";"";"";"Crystal:Crystal_SMD_Abracon_ABM8AIG-4Pin_3.2x2.5mm";"https://www.lcsc.com/datasheet/C1669787.pdf"

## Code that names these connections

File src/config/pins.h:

#pragma once
// ============================================================
//  pins.h — SCLF Gripper Pin Definitions
//  VERIFIED directly from SCLF_Gripper.kicad_sch
//  Single source of truth. Never use magic numbers elsewhere.
//  Board: STM32G474CEU6 | Date: 2026-04-15
// ============================================================

// ─── SWD / Programming pads (managed by debugger) ───────────
// PA13 = SWDIO, PA14 = SWCLK — do NOT reconfigure these as GPIO
// PG10 = RST (also SWD reset)

// ─── Boot & Reset ────────────────────────────────────────────
#define PIN_BOOT        PB8     // BOOT0 button — hold during reset for DFU mode
#define PIN_RESET       PG10    // Hardware reset button

// ─── DRV8316C Gate Driver (SPI — shared bus with PB3/4/5) ───
// nFAULT is routed to PC13. DRVOFF is tied to GND (always enabled).
#define PIN_DRV_FAULT   PC13    // DRV8316 nFAULT — Hardware fault indicator (active low)
#define PIN_DRV_CS      PC4     // DRV8316 nSCS  — SPI Chip Select (active low)
#define PIN_DRV_CLK     PB3     // DRV8316 SCLK  — SPI Clock  (SPI1)
#define PIN_DRV_MISO    PB4     // DRV8316 SDO   — SPI MISO   (SPI1)
#define PIN_DRV_MOSI    PB5     // DRV8316 SDI   — SPI MOSI   (SPI1)

// ─── Motor PWM outputs (DRV8316 INH/INL ← HRTIM/TIM) ───────
// High-side (INHA=PA10, INHB=PA9, INHC=PA8 on DRV8316)
#define PIN_AH          PA10    // Phase A High
#define PIN_BH          PA9     // Phase B High
#define PIN_CH          PA8     // Phase C High
// Low-side (INLA=PB15, INLB=PB14, INLC=PB13 on DRV8316)
#define PIN_AL          PB15    // Phase A Low
#define PIN_BL          PB14    // Phase B Low
#define PIN_CL          PB13    // Phase C Low

// ─── Inline Current Sense ADC (DRV8316 SOA/SOB/SOC) ─────────
#define PIN_CURA        PA0     // Phase A current sense (ADC1_IN1)
#define PIN_CURB        PA1     // Phase B current sense (ADC1_IN2)
#define PIN_CURC        PA2     // Phase C current sense (ADC1_IN3) — also test pad

// ─── Voltage Sense ───────────────────────────────────────────
#define PIN_VSENS       PB11    // DC bus voltage sense (ADC)

// ─── MT6701 Magnetic Encoder (SPI — separate CS) ────────────
// Max SPI clock: 10 MHz. Use SPISettings(5000000, MSBFIRST, SPI_MODE0)
#define PIN_ENC_CS      PA4     // MT6701 ~CS  (active low)
#define PIN_ENC_CLK     PA5     // MT6701 CLK
#define PIN_ENC_SDO     PA6     // MT6701 SDO  (MISO — read only, no MOSI needed)

// ─── RS-485 (MAX3485 — UART3 / half-duplex) ─────────────────
#define PIN_RS485_TX    PC10    // UART TX → MAX3485 DI
#define PIN_RS485_RX    PC11    // UART RX ← MAX3485 RO
#define PIN_RS485_DIR   PB9     // DE/RE control: HIGH=TX, LOW=RX

// ─── USB Virtual COM Port ────────────────────────────────────
// PA11 = USB_DM (D-), PA12 = USB_DP (D+) — fixed hardware, no defines needed

// ─── LED ─────────────────────────────────────────────────────
#define PIN_LED         PC6     // Status LED

// ─── Crystal (16 MHz HSE) ────────────────────────────────────
// PF0 = OSC_IN, PF1 = OSC_OUT — configured as HSE, do NOT use as GPIO

// ─── Reserved (appear in schematic, function unknown) ────────
// PB6, PB7, PA15 — do not assign without schematic review

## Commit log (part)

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2026-02-11 Kicad schematic
2026-02-11 Create hardware
2026-02-11 Create sch
2026-02-11 Kicad PCB
2026-02-11 Create img
2026-02-11 Update Gripper_info image link in README
2026-02-25 chore: move hardware files and images to repository structure
2026-02-25 Fix Windows SimpleFOC compilation bugs, paths, and hardware initialization code
2026-02-26 Update MEMORY and AI artifacts to reflect working compiled firmware and PlatformIO configs
2026-02-26 Translate project documentation to Euskera and setup multilingual READMEs (EN, EU, ES)
2026-02-26 Rename files to make Euskara the default README
2026-03-04 docs: Update extension download URLs and clarify OpenOCD installation
2026-03-04 docs: Add modular architecture and hardware safety rules
2026-03-04 docs: Add clarification on DFU bootloader and PA9/VBUS sensing on STM32G4
2026-03-04 docs: Explain limitations of USB DFU vs ST-Link debugging
2026-03-04 feat/test: fase 1.1 - MT6701 sentsorearen standalone test-a prest
2026-03-04 docs: Add solution for genericSTM32G474CE board recognition error
2026-03-04 build: Update SimpleFOC dependency to match remote configuration
2026-03-04 docs: Add board recognition fix to Spanish and English READMEs
2026-03-04 docs: Keep Euskara README as default and add translated fix
2026-03-04 docs: Firmware garapen plana (Roadmap) gehitu da proiektura
2026-03-04 test: Fase 1.1-en kodigoa 'examples' karpetan gorde da etorkizunerako
2026-03-04 docs: Adibideen karpeta (examples) eta 1.1 faseko testaren argibideak gehitu dira
2026-03-04 feat: Faseak automatizatzeko IA workflow-ak (hasi eta amaitu) gehitu dira
2026-03-04 feat: Fase 1.2 DRV8316 SPI Test amaituta
2026-03-05 docs: 1_3_open_loop_v_control amaituta eta examples karpetan eskuragarri
2026-03-05 docs: rename 1.3 example folder to fase1_3_open_loop_v_control
2026-03-05 docs: fase4_2_rs485 amaituta eta examples karpetan eskuragarri
2026-03-05 docs: fase3_2_gripper_kinematics amaituta eta examples karpetan eskuragarri
2026-03-06 feat: enable USB CDC VCP + custom upload via STM32CubeProgrammer
    - platformio.ini: upload_protocol=custom using STM32CubeProgrammer CLI (bypasses PIO registry timeout)
    - platformio.ini: added -DUSBCON -DUSBD_USE_CDC -DHAL_PCD_MODULE_ENABLED for USB VCP on PA11/PA12
    - src/main.cpp: loaded fase1_1_mt6701_test (MT6701 standalone test, motor disabled)
2026-03-07 docs: Fase 1.4 RS485 loopback terminada + Encoder 3.3V verificado
2026-03-11 Backup of working changes before starting new phase
2026-03-11 Update Fase 1.1 documentation and sensor logic
2026-03-12 docs: fase1_1_mt6701_test amaituta eta examples karpetan eskuragarri
2026-03-13 docs: add Git installation step to READMEs
2026-03-13 docs: fase1_2_drv_spi_test amaituta eta examples karpetan eskuragarri
2026-03-16 chore: optimize foc-hardware-setup skill to read markdown instead of kicad files
2026-03-16 chore: enable PIO multi-environment compilation to speed up testing
2026-03-24 docs: add driver to MCU connections mapping
2026-03-24 hardware: update pin mapping for v2 PCB (swap AL and CL)
2026-03-24 docs: fase1_4_rs485_ping amaituta eta examples karpetan eskuragarri
2026-03-24 docs: repository cleanup and developer handoff notes
2026-03-24 docs: add critical warning to read TASKS.md before starting
2026-03-24 docs: add multi-language backlog tracking (eu, es, en)
2026-03-24 feat(tasks): add automatic startup warning to read TASKS.md
2026-03-26 docs: sync translated task lists with phase 4 results
2026-03-26 Rename 548244301-b4852472-1715-4a92-b645-8ac5ee7b4d7d.jpg to Infography.jpg
2026-04-14 Rename SCLF_Gripper_v1.0.kicad_pcb to SCLF_Gripper.kicad_pcb
2026-04-14 Cleanup: Remove v1.0 suffix from hardware files
2026-04-15 docs: update pinout, images to PNG and hardware design files
2026-04-15 docs: reset documentation and tasks for new prototype validation
2026-04-15 docs: complete phase 1.2 drv spi validation on new prototype
2026-04-15 docs: finalize phase 1.3 motor open loop validation on new prototype
2026-04-15 docs: synchronize all TASKS files with v2.0 hardware achievements (Phases 1.1-1.3)
2026-04-16 docs: finalize Phase 1.4 RS485 Ping and refine driver
2026-04-16 chore: start phase 1.5 current sense
2026-04-16 feat(phase1.5): finalize current sense validation and fix SPI protocol bug
2026-04-16 docs: update task lists in all languages for Phase 1.5 completion
2026-04-16 fix: corrigo sintaxis y estructura en el test de open loop (Phase 1.3)
2026-04-19 Phase 2.1: Implement MotorController and Open-Loop FOC test
2026-04-19 Phase 2.2: Implement Closed-Loop FOC test and diagnostic tools
2026-04-21 fix(encoder): MT6701::update() calls Sensor::update() for correct FOC velocity tracking - doc: update fase2_2 README with test results and speed ramp instructions
2026-04-21 docs: mark phase 2.2 as completed in all languages
2026-04-21 docs: reorder phases to prioritize communication and safety infrastructure
2026-04-21 Rename fase folders to phase in examples directory
2026-04-21 feat: complete Phase 4.1 basic RS485 test, rename example, and update tasks
2026-04-21 chore: update platformio.ini path for phase4_1_rs485_basic
2026-04-21 feat: implement full RS485 control protocol with shorthand support and update tasks
2026-04-21 chore: fix phase numbering from 4 to 3 in examples and tasks
2026-04-22 Phase 4: USB VCP and Commander implementation validated
2026-04-22 Phase 5: Fault Manager implementation validated with mechanical stall test
2026-04-22 Phase 5: Refined README with precise testing instructions
2026-04-22 Phase 6: Persistence implementation validated with dual-bank fix
2026-04-28 Standardize documentation: update environment commands and remove copy instructions
2026-04-28 WIP: Motor-Encoder alignment and phase 7 infrastructure
2026-05-05 Phase 7.1 Complete: Motor-Encoder Alignment, Advanced Tuning Infrastructure, and Multi-language Documentation Updates
2026-05-05 docs: actualizar MEMORY.md con parámetros PID de fase 7.1
